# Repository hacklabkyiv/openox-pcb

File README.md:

# openox-pcb
PCB design for OpenOx - open source oxygen concentrator

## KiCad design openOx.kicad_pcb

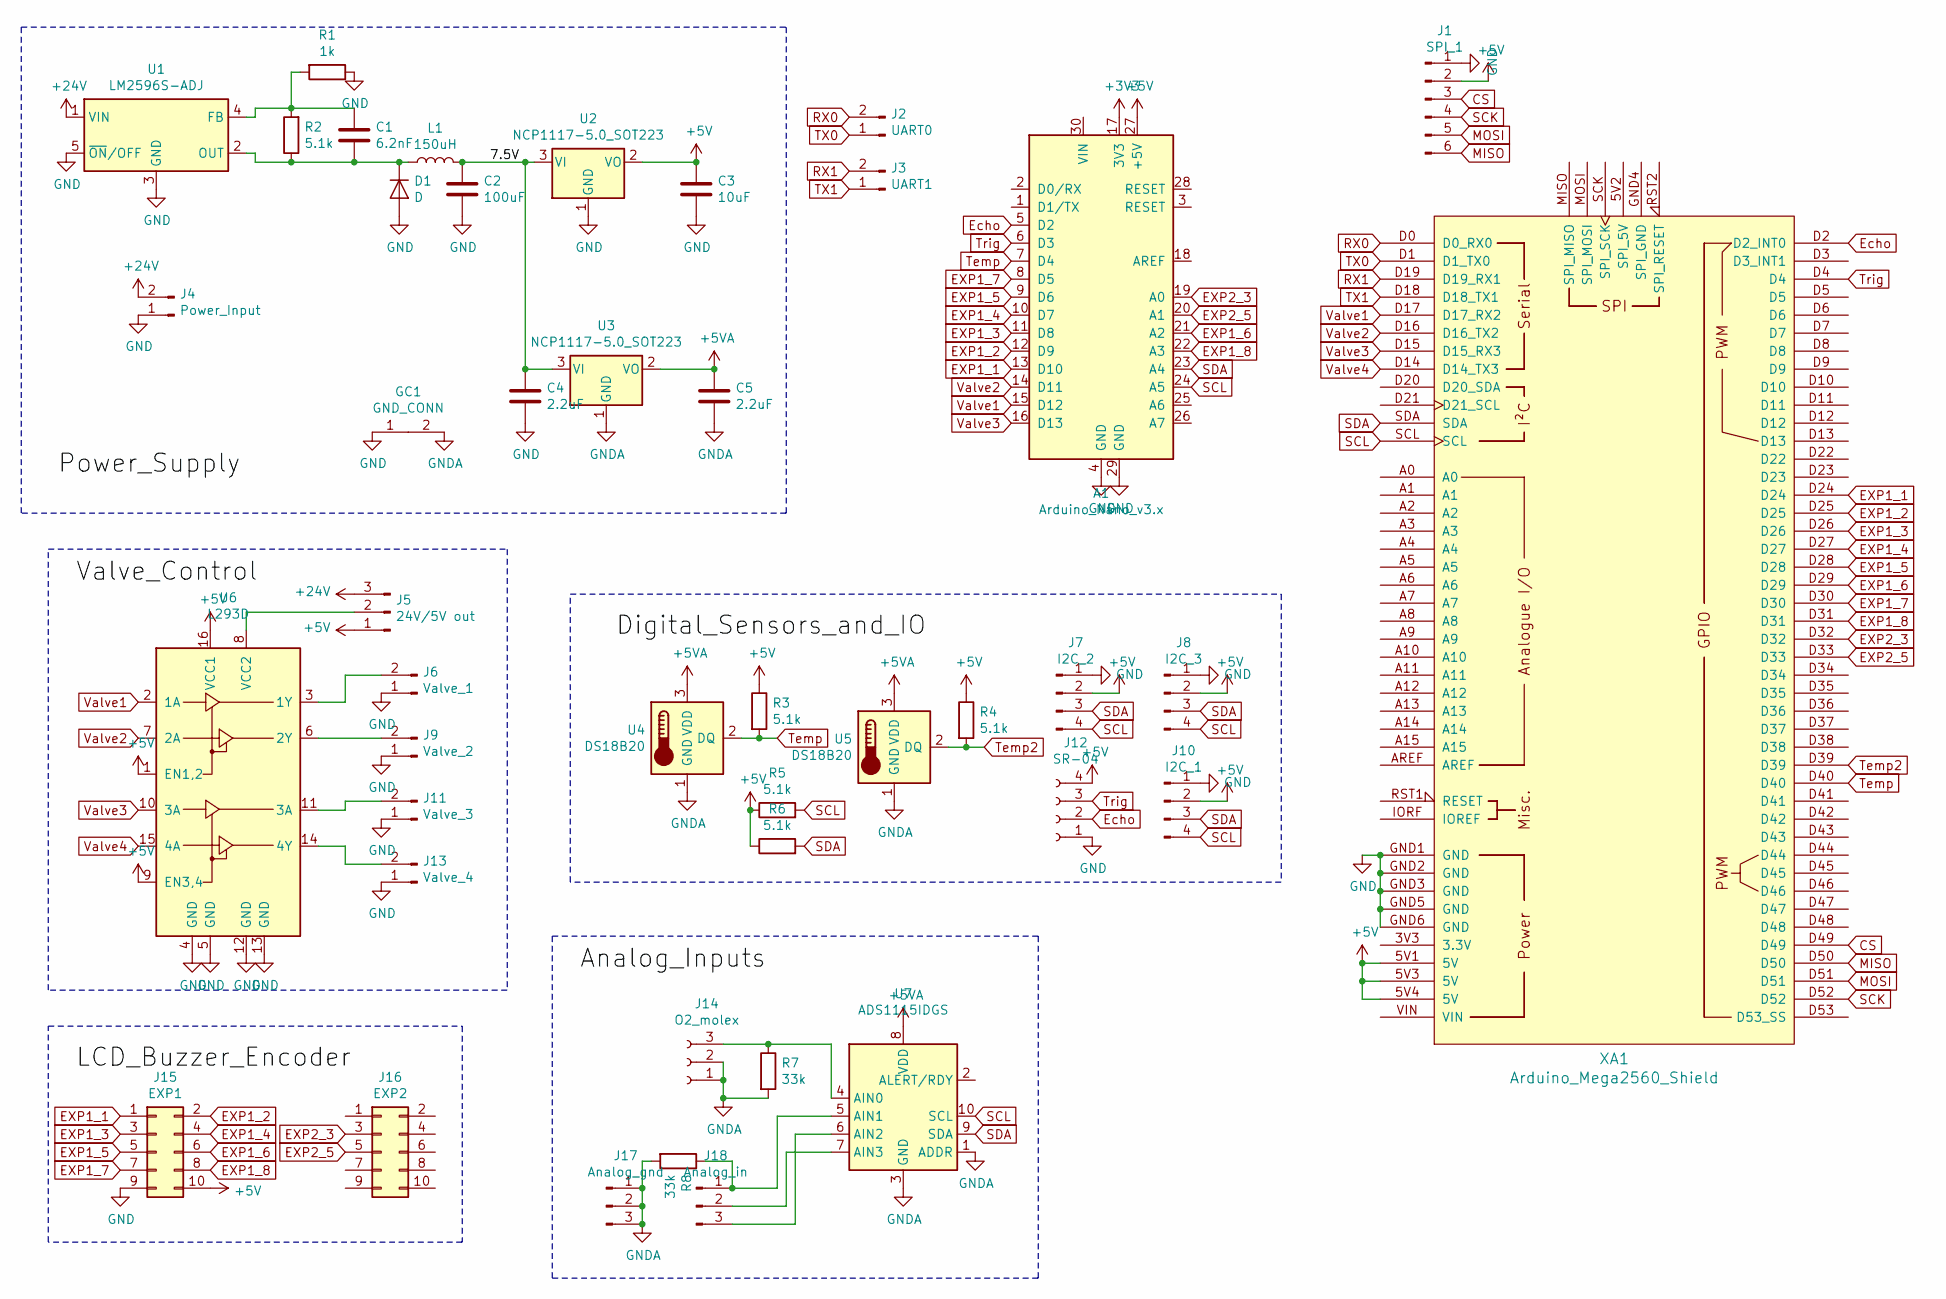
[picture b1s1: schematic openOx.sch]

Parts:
A1: Arduino_Nano_v3.x; Arduino_Nano
C1: 6.2nF; C_0805_2012Metric
C2: 100uF; C_1206_3216Metric
C3: 10uF; C_0805_2012Metric
C4, C5: 2.2uF; C_0805_2012Metric
D1: D; D_SOD-123
GC1: GND_CONN
J1: SPI_1; PinHeader_1x06_P2.54mm_Vertical
J2: UART0; PinHeader_1x02_P2.54mm_Vertical
J3: UART1; PinHeader_1x02_P2.54mm_Vertical
J4: Power_Input; TerminalBlock_TE_282834-2_1x02_P2.54mm_Horizontal
J5: 24V/5V out; PinHeader_1x03_P2.54mm_Vertical
J6: Valve_1; TerminalBlock_TE_282834-2_1x02_P2.54mm_Horizontal
J7: I2C_2; PinHeader_1x04_P2.54mm_Vertical
J8: I2C_3; PinHeader_1x04_P2.54mm_Vertical
J9: Valve_2; TerminalBlock_TE_282834-2_1x02_P2.54mm_Horizontal
J10: I2C_1; PinHeader_1x04_P2.54mm_Vertical
J11: Valve_3; TerminalBlock_TE_282834-2_1x02_P2.54mm_Horizontal
J12: SR-04; PinHeader_1x04_P2.54mm_Vertical
J13: Valve_4; TerminalBlock_TE_282834-2_1x02_P2.54mm_Horizontal
J14: O2_molex; Molex_KK-254_AE-6410-03A_1x03_P2.54mm_Vertical
J15: EXP1; IDC-Header_2x05_P2.54mm_Vertical
J16: EXP2; IDC-Header_2x05_P2.54mm_Vertical
J17: Analog_gnd; PinHeader_1x03_P2.54mm_Vertical
J18: Analog_in; PinHeader_1x03_P2.54mm_Vertical
L1: 150uH; L_Bourns_SRR1260
R1: 1k; R_0805_2012Metric
R2, R3, R4, R5, R6: 5.1k; R_0805_2012Metric
R7, R8: 33k; R_0805_2012Metric
U1: LM2596S-ADJ; TO-263-5_TabPin3
U2, U3: NCP1117-5.0_SOT223; SOT-223-3_TabPin2
U4, U5: DS18B20; PinHeader_1x03_P2.54mm_Vertical
U6: L293D; DIP-16_W7.62mm
U7: ADS1115IDGS; TSSOP-10_3x3mm_P0.5mm
XA1: Arduino_Mega2560_Shield

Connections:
+3V3: A1.17 (3V3)
+5V: A1.27 (+5V), C3.1, J1.2, J5.1, J7.2, J8.2, J10.2, J12.4, J15.10, R3.1, R4.1, R5.1, R6.1, U2.2 (VO), U6.1 (EN1,2), U6.9 (EN3,4), U6.16 (VCC1), XA1.5V1 (5V), XA1.5V3 (5V), XA1.5V4 (5V)
+5VA: C5.1, U3.2 (VO), U4.3 (VDD), U5.3 (VDD), U7.8 (VDD)
+24V: J4.2, J5.3, U1.1 (VIN)
/7.5V: C2.1, C4.1, L1.2, U2.3 (VI), U3.3 (VI)
CS: J1.3, XA1.D49
EXP1_1: A1.13 (D10), J15.1, XA1.D24
EXP1_2: A1.12 (D9), J15.2, XA1.D25
EXP1_3: A1.11 (D8), J15.3, XA1.D26
EXP1_4: A1.10 (D7), J15.4, XA1.D27
EXP1_5: A1.9 (D6), J15.5, XA1.D28
EXP1_6: A1.21 (A2), J15.6, XA1.D29
EXP1_7: A1.8 (D5), J15.7, XA1.D30
EXP1_8: A1.22 (A3), J15.8, XA1.D31
EXP2_3: A1.19 (A0), J16.3, XA1.D32
EXP2_5: A1.20 (A1), J16.5, XA1.D33
Echo: A1.5 (D2), J12.2, XA1.D2 (D2_INT0)
GND: A1.4 (GND), A1.29 (GND), C2.2, C3.2, C4.2, D1.2 (A), GC1.1, J1.1, J4.1, J6.1, J7.1, J8.1, J9.1, J10.1, J11.1, J12.1, J13.1, J15.9, R1.1, U1.3 (GND), U1.5 (~ON~/OFF), U2.1 (GND), U6.4 (GND), U6.5 (GND), U6.12 (GND), U6.13 (GND), XA1.GND1 (GND), XA1.GND2 (GND), XA1.GND3 (GND), XA1.GND5 (GND), XA1.GND6 (GND)
GNDA: C5.2, GC1.2, J14.1, J14.2, J17.1, J17.2, J17.3, R7.2, R8.2, U3.1 (GND), U4.1 (GND), U5.1 (GND), U7.1 (ADDR), U7.3 (GND)
MISO: J1.6, XA1.D50
MOSI: J1.5, XA1.D51
unnamed: C1.1, R1.2, R2.2, U1.4 (FB)
unnamed: C1.2, D1.1 (K), L1.1, R2.1, U1.2 (OUT)
unnamed: J5.2, U6.8 (VCC2)
unnamed: J6.2, U6.3 (1Y)
unnamed: J9.2, U6.6 (2Y)
unnamed: J11.2, U6.11 (3A)
unnamed: J13.2, U6.14 (4Y)
unnamed: J14.3, R7.1, U7.4 (AIN0)
unnamed: J18.1, R8.1, U7.5 (AIN1)
unnamed: J18.2, U7.7 (AIN3)
unnamed: J18.3, U7.6 (AIN2)
RX0: J2.2, XA1.D0 (D0_RX0)
RX1: J3.2, XA1.D19 (D19_RX1)
SCK: J1.4, XA1.D52
SCL: A1.24 (A5), J7.4, J8.4, J10.4, R5.2, U7.10 (SCL), XA1.SCL
SDA: A1.23 (A4), J7.3, J8.3, J10.3, R6.2, U7.9 (SDA), XA1.SDA
TX0: J2.1, XA1.D1 (D1_TX0)
TX1: J3.1, XA1.D18 (D18_TX1)
Temp: A1.7 (D4), R3.2, U4.2 (DQ), XA1.D40
Temp2: R4.2, U5.2 (DQ), XA1.D39
Trig: A1.6 (D3), J12.3, XA1.D4
Valve1: A1.15 (D12), U6.2 (1A), XA1.D17 (D17_RX2)
Valve2: A1.14 (D11), U6.7 (2A), XA1.D16 (D16_TX2)
Valve3: A1.16 (D13), U6.10 (3A), XA1.D15 (D15_RX3)
Valve4: U6.15 (4A), XA1.D14 (D14_TX3)

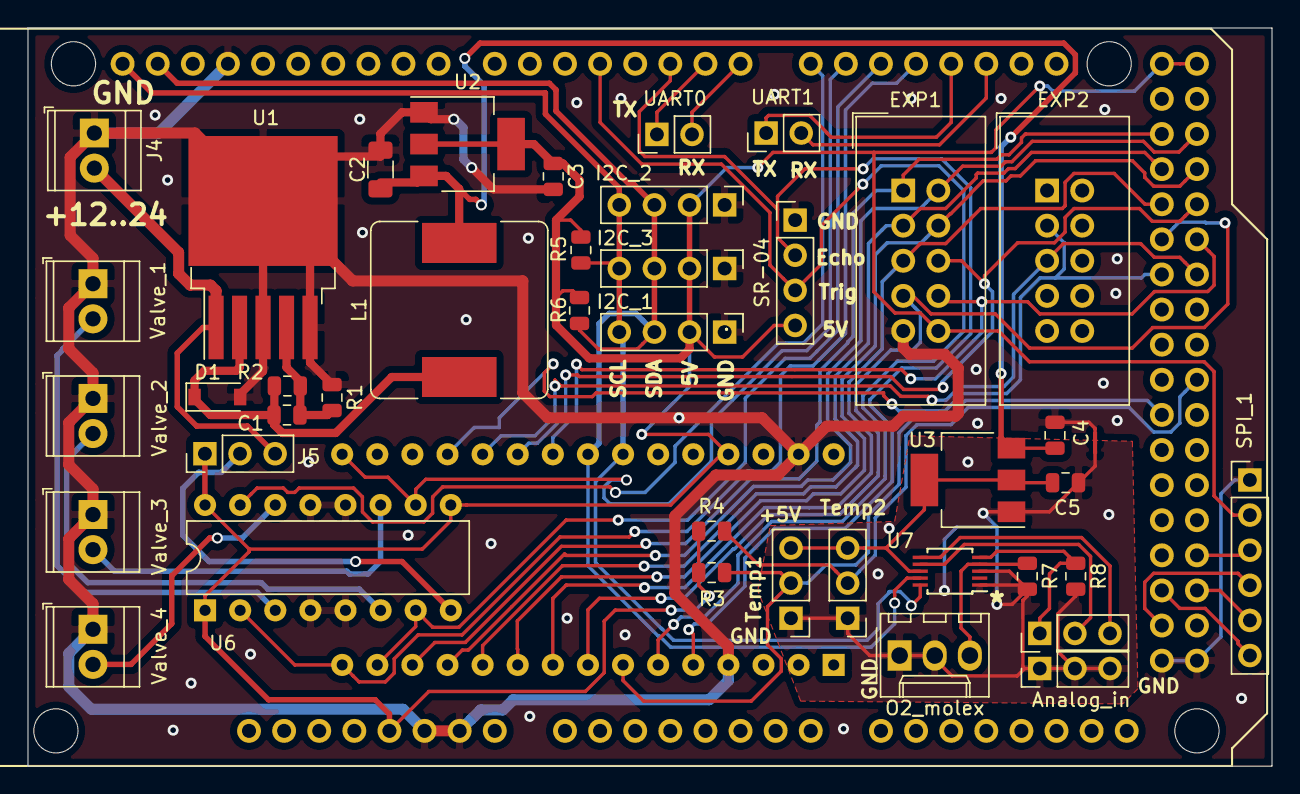
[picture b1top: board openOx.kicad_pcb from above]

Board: 2 copper layers, 90.0 x 53.4 mm, 43 parts (1 on the bottom side), 45 nets.

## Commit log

2020-04-03 first PCB revision in KiCAD and corresponding gerbers in .zip
2020-04-03 Deleted old schematics, was uploaded by mistake
2020-04-06 outline changed, C2 package changed
